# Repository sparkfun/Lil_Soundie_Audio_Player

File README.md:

SparkFun Little Soundie Audio Player
========================================

[*SparkFun Little Soundie (14006)*](https://www.sparkfun.com/products/14006)

The Little Soundie Audio Player is a breakout board for the VS1000D, an audio decoder capable of playing OGG and WAV type audio files. 
The Little Soundie makes adding sound effects to your project, prop, or costume easily with the built-in USB mass storage for your audio file and simple methods of triggering audio playback.  

Repository Contents
-------------------

* **/Firmware** - VLSI - VS1000D Firmware
* **/Hardware** - Eagle design files (.brd, .sch)
* **/Production** - Production panel files (.brd)
* **/Software** - An easy to use Arduino Template in case you want to hook up your Little Soundie to a Redboard or any board programmed with Arduino.

Documentation
--------------
* **[Hookup Guide](https://learn.sparkfun.com/tutorials/little-soundie-audio-player-hookup-guide)** - Basic hookup guide for the Little Soundie Audio Player.
* **[SparkFun Fritzing repo](https://github.com/sparkfun/Fritzing_Parts)** - Fritzing diagrams for SparkFun products. 

License Information
-------------------

This product is _**open source**_! 

Please review the LICENSE.md file for license information. 

If you have any questions or concerns on licensing, please contact techsupport@sparkfun.com.

Distributed as-is; no warranty is given.

- Your friends at SparkFun.

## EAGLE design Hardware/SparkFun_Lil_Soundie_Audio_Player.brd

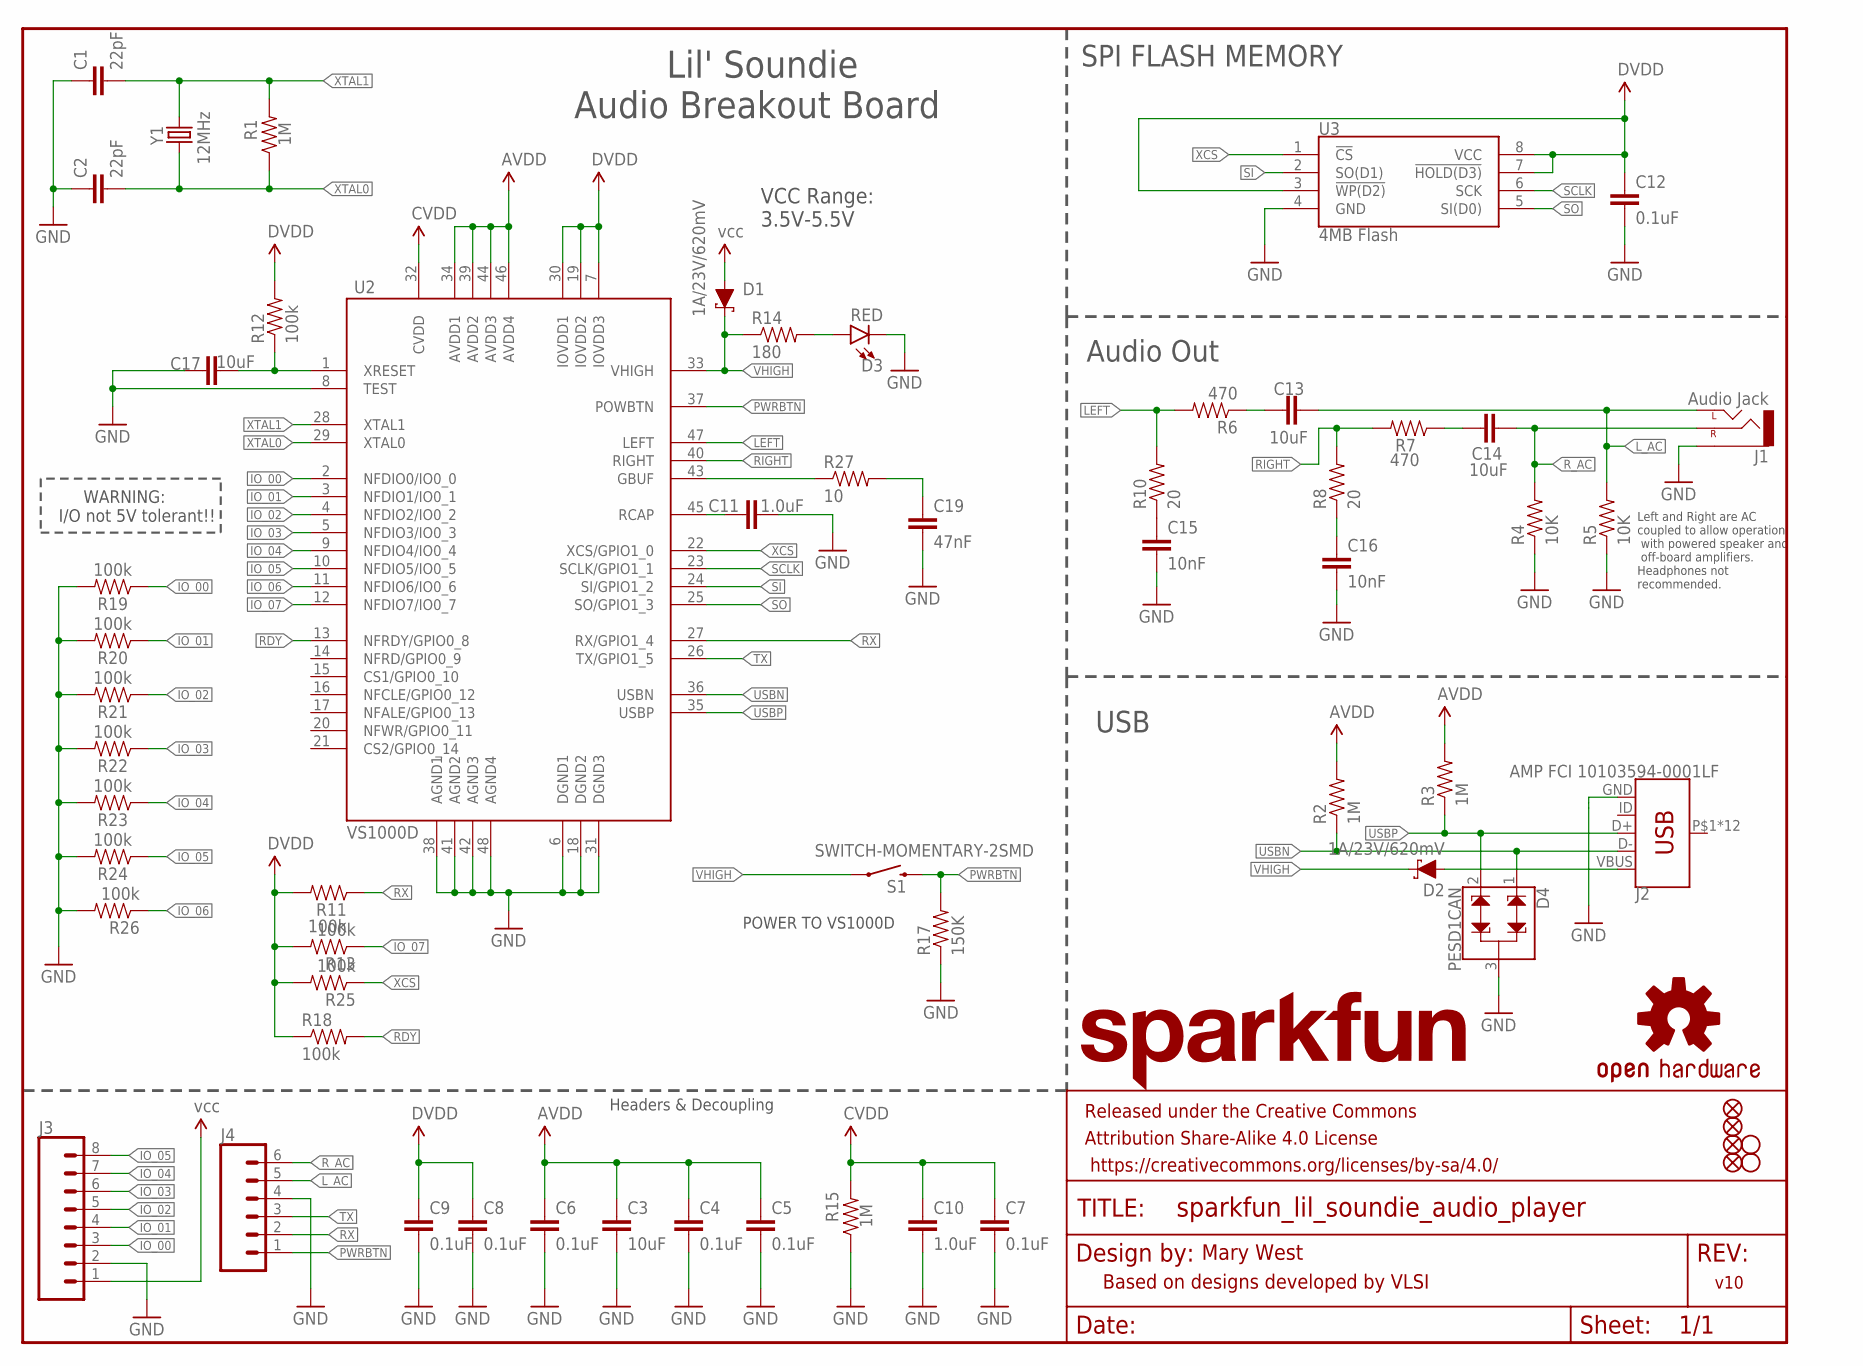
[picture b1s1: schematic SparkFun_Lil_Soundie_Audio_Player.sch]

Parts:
C1, C2: 22pF; 0603-CAP
C3, C13, C14, C17: 10uF; 0603-CAP
C4, C5, C6, C7, C8, C9, C12: 0.1uF; 0603-CAP
C10, C11: 1.0uF; 0603-CAP
C15, C16: 10nF; 0603-CAP
C19: 47nF; 0603-CAP
D1, D2: 1A/23V/620mV; SOD-323
D3: RED; LED-0603
D4: PESD1CAN; SOT23-3
FD1, FD2, FD3, FD4: FIDUCIALUFIDUCIAL; FIDUCIAL-MICRO
FRAME1: FRAME-LETTER; CREATIVE_COMMONS
H1, H4: STAND-OFFTIGHT; STAND-OFF-TIGHT
J1: Audio Jack; AUDIO-JACK-3.5MM-SMD
J2: AMP FCI 10103594-0001LF; USB-MICROB-PTH
J3: CONN_08"; 1X08
J4: CONN_06SILK_FEMALE_PTH; 1X06
LOGO1: OSHW-LOGOL; OSHW-LOGO-L
LOGO2: SFE_LOGO_NAME.1_INCH; SFE_LOGO_NAME_.1
R1, R2, R3, R15: 1M; 0603-RES
R4, R5: 10K; 0603-RES
R6, R7: 470; 0603-RES
R8, R10: 20; 0603-RES
R11, R12, R13, R18, R25, R26: 100k; 0603-RES
R14: 180; 0603-RES
R17: 150K; 0603-RES
R19, R20, R21, R22, R23, R24: 100k; 0603
R27: 10; 0603-RES
S1: SWITCH-MOMENTARY-2SMD; TACTILE-SWITCH-SMD
U2: VS1000D; LQFP-48
U3: 4MB Flash; SO08
Y1: 12MHz; CRYSTAL-SMD-5X3

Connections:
AVDD: C3.1, C4.1, C5.1, C6.1, R2.2, R3.2, U2.34 (AVDD1), U2.39 (AVDD2), U2.44 (AVDD3), U2.46 (AVDD4)
CVDD: C7.1, C10.1, R15.2, U2.32 (CVDD)
DVDD: C8.1, C9.1, C12.1, R11.2, R12.2, R13.2, R18.1, R25.2, U2.7 (IOVDD3), U2.19 (IOVDD2), U2.30 (IOVDD1), U3.3 (!WP(D2)), U3.7 (!HOLD(D3)), U3.8 (VCC)
GBUF: R27.1, U2.43 (GBUF)
GND: C1.1, C2.1, C3.2, C4.2, C5.2, C6.2, C7.2, C8.2, C9.2, C10.2, C11.2, C12.2, C15.2, C16.2, C17.1, C19.2, D3.C, D4.3, J1.SLEEVE, J2.GND, J3.2, J4.4, R4.1, R5.1, R15.1, R17.1, R19.2, R20.2, R21.2, R22.2, R23.2, R24.2, R26.2, U2.6 (DGND1), U2.8 (TEST), U2.18 (DGND2), U2.31 (DGND3), U2.38 (AGND1), U2.41 (AGND2), U2.42 (AGND3), U2.48 (AGND4), U3.4 (GND)
IO_00: J3.3, R19.1, U2.2 (NFDIO0/IO0_0)
IO_01: J3.4, R20.1, U2.3 (NFDIO1/IO0_1)
IO_02: J3.5, R21.1, U2.4 (NFDIO2/IO0_2)
IO_03: J3.6, R22.1, U2.5 (NFDIO3/IO0_3)
IO_04: J3.7, R23.1, U2.9 (NFDIO4/IO0_4)
IO_05: J3.8, R24.1, U2.10 (NFDIO5/IO0_5)
IO_06: R26.1, U2.11 (NFDIO6/IO0_6)
IO_07: R13.1, U2.12 (NFDIO7/IO0_7)
LEFT: R6.2, R10.2, U2.47 (LEFT)
L_AC: C13.2, J1.TIP (LEFT), J4.5, R5.2
unnamed: C19.1, R27.2
unnamed: C13.1, R6.1
unnamed: C15.1, R10.1
unnamed: C11.1, U2.45 (RCAP)
unnamed: C17.2, R12.1, U2.1 (XRESET)
unnamed: D2.A, J2.VBUS
unnamed: C14.1, R7.1
unnamed: D3.A, R14.2
unnamed: C16.1, R8.1
PWRBTN: J4.1, R17.2, S1.3 (2), U2.37 (POWBTN)
RDY: R18.2, U2.13 (NFRDY/GPIO0_8)
RIGHT: R7.2, R8.2, U2.40 (RIGHT)
RX: J4.2, U2.27 (RX/GPIO1_4)
R_AC: C14.2, J1.RING (RIGHT), J4.6, R4.2
SCLK: U2.23 (SCLK/GPIO1_1), U3.6 (SCK)
SI: U2.24 (SI/GPIO1_2), U3.2 (SO(D1))
SO: U2.25 (SO/GPIO1_3), U3.5 (SI(D0))
TX: J4.3, U2.26 (TX/GPIO1_5)
USBN: D4.1, J2.D-, R2.1, U2.36 (USBN)
USBP: D4.2, J2.D+, R3.1, U2.35 (USBP)
VCC: D1.A, J3.1
VHIGH: D1.C, D2.C, R14.1, S1.1, U2.33 (VHIGH)
XCS: R25.1, U2.22 (XCS/GPIO1_0), U3.1 (!CS)
XTAL0: C2.2, R1.1, U2.29 (XTAL0), Y1.1
XTAL1: C1.2, R1.2, U2.28 (XTAL1), Y1.3 (2)

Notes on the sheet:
Mary West
v10
VCC Range: 3.5V-5.5V
SPI FLASH MEMORY
Headers & Decoupling
POWER TO VS1000D
Left and Right are AC coupled to allow operation with powered speaker and off-board amplifiers. Headphones not recommended.
Based on designs developed by VLSI
WARNING: I/O not 5V tolerant!!
USB
Audio Out
Lil' Soundie Audio Breakout Board

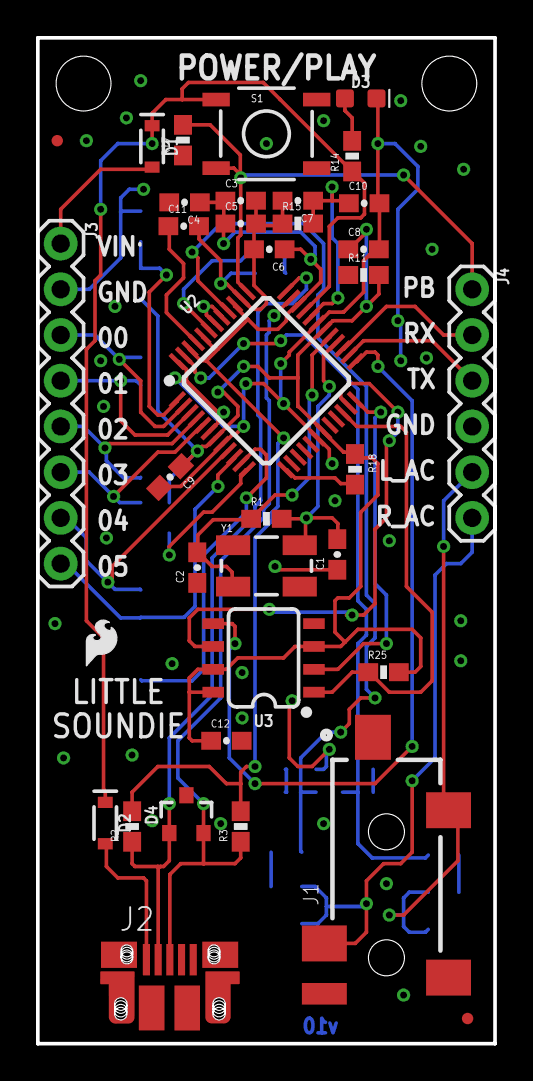
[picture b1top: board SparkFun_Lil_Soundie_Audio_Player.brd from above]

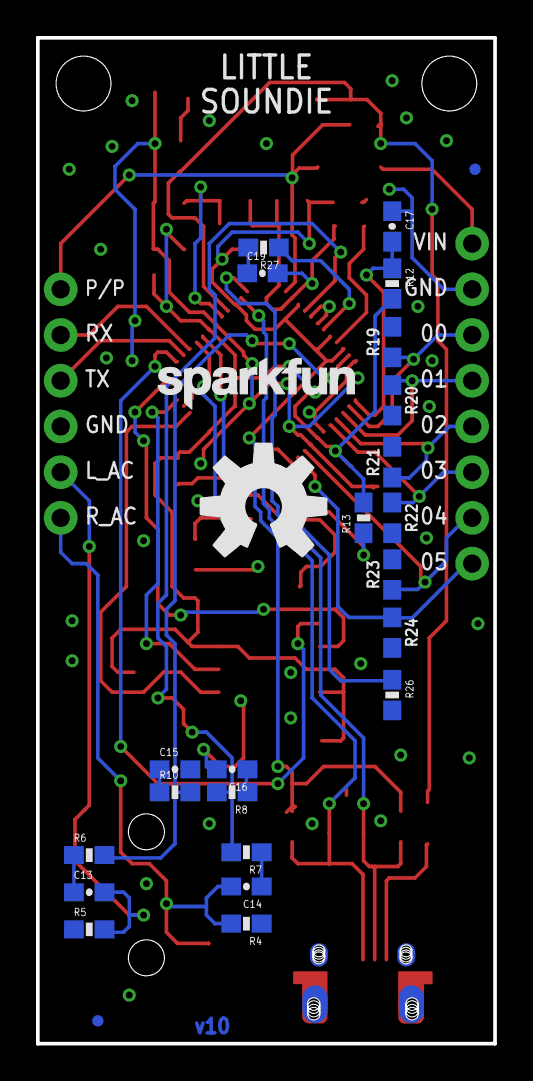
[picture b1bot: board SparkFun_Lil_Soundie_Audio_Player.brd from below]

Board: 2 copper layers, 25.4 x 55.9 mm, 65 parts (26 on the bottom side), 40 nets.

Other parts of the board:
U$1: SFE_LOGO_FLAME_.1

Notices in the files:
parts and their libraries:
SparkFun-Aesthetics: Licensing: Creative Commons ShareAlike 4.0 International - https://creativecommons.org/licenses/by-sa/4.0
SparkFun-Aesthetics: Released under the Creative Commons Attribution Share-Alike 4.0 License
SparkFun-Aesthetics: https://creativecommons.org/licenses/by-sa/4.0
